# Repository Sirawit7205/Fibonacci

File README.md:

# Fibonacci
16-bit Fibonacci calculator with logic ICs

A circuit that calculates fibonacci up to 46,368 using only logic chips (except the display).

This project is mostly intended as a soldering practice because the PIC microcontroller featured on the board is fully capable of calculating fibonacci anyway without all the logic chips.

There are two versions of PCB, through-hole and SMD. Both versions use the same circuit and have the same physical size (4x6 inches: will fit most postcard frames).

The only difference is the PIC microcontroller used, both code also work the same way.

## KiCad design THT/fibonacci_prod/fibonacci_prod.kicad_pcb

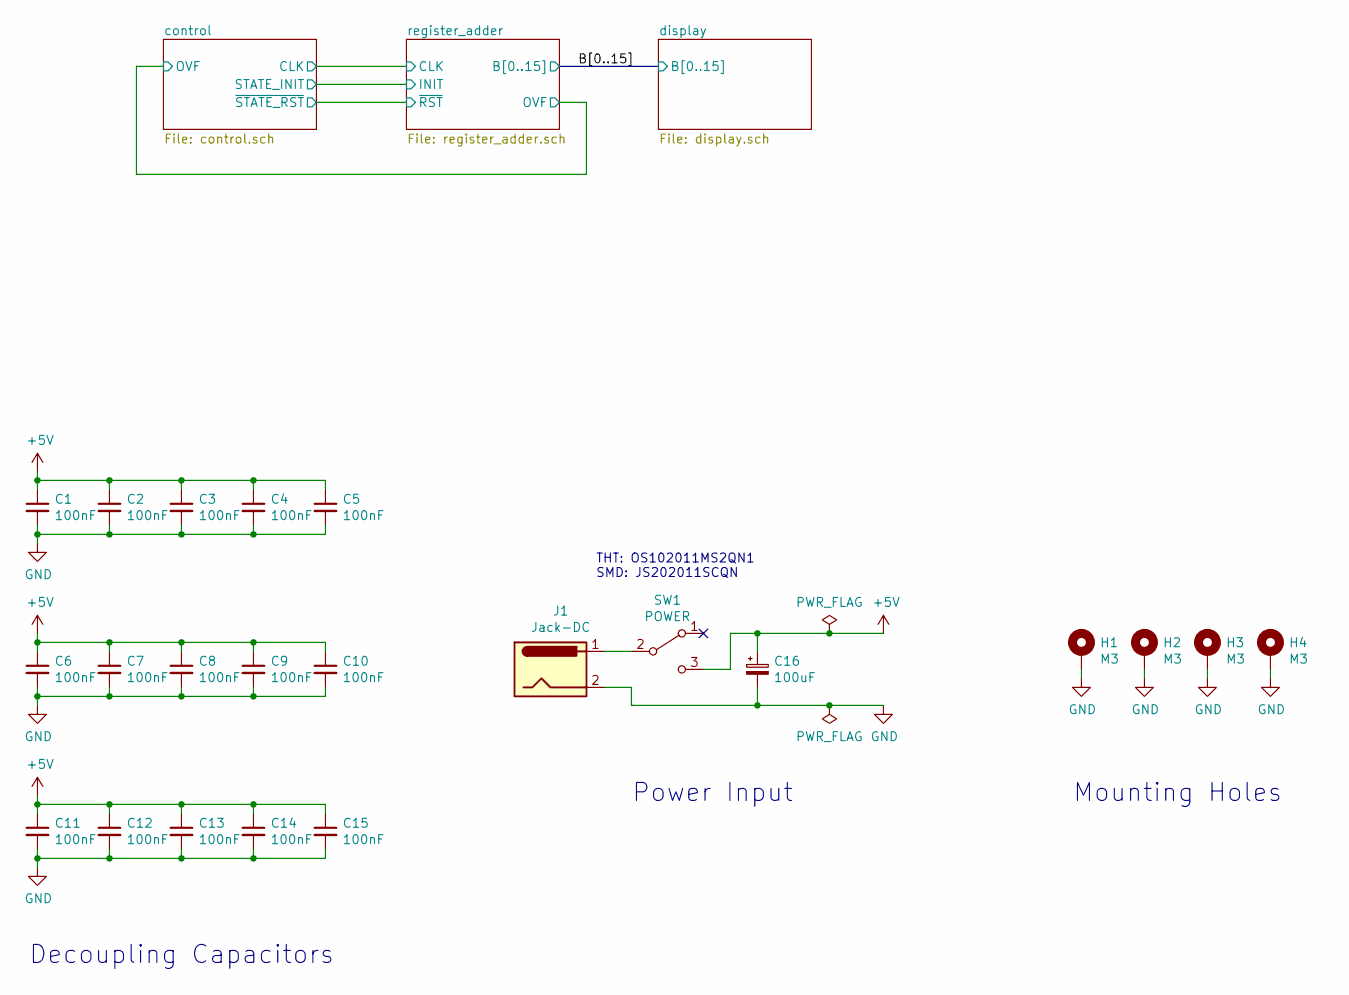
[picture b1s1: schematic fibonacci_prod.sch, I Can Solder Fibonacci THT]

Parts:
C1, C2, C3, C4, C5, C6, C7, C8, C9, C10, C11, C12, C13, C14, C15: 100nF; C_Disc_D5.1mm_W3.2mm_P5.00mm
C16: 100uF; CP_Radial_D6.3mm_P2.50mm
H1, H2, H3, H4: M3; MountingHole_3mm_Pad
J1: Jack-DC; BarrelJack_Horizontal
SW1: POWER; OS102011MS2QN1

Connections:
+5V: C1.1, C2.1, C3.1, C4.1, C5.1, C6.1, C7.1, C8.1, C9.1, C10.1, C11.1, C12.1, C13.1, C14.1, C15.1, C16.1, SW1.3 (C); also elsewhere on the board
GND: C1.2, C2.2, C3.2, C4.2, C5.2, C6.2, C7.2, C8.2, C9.2, C10.2, C11.2, C12.2, C13.2, C14.2, C15.2, C16.2, H1.1, H2.1, H3.1, H4.1, J1.2; also elsewhere on the board
unnamed: J1.1, SW1.2 (B)

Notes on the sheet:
Decoupling Capacitors
Power Input
THT: OS102011MS2QN1 SMD: JS202011SCQN
Mounting Holes

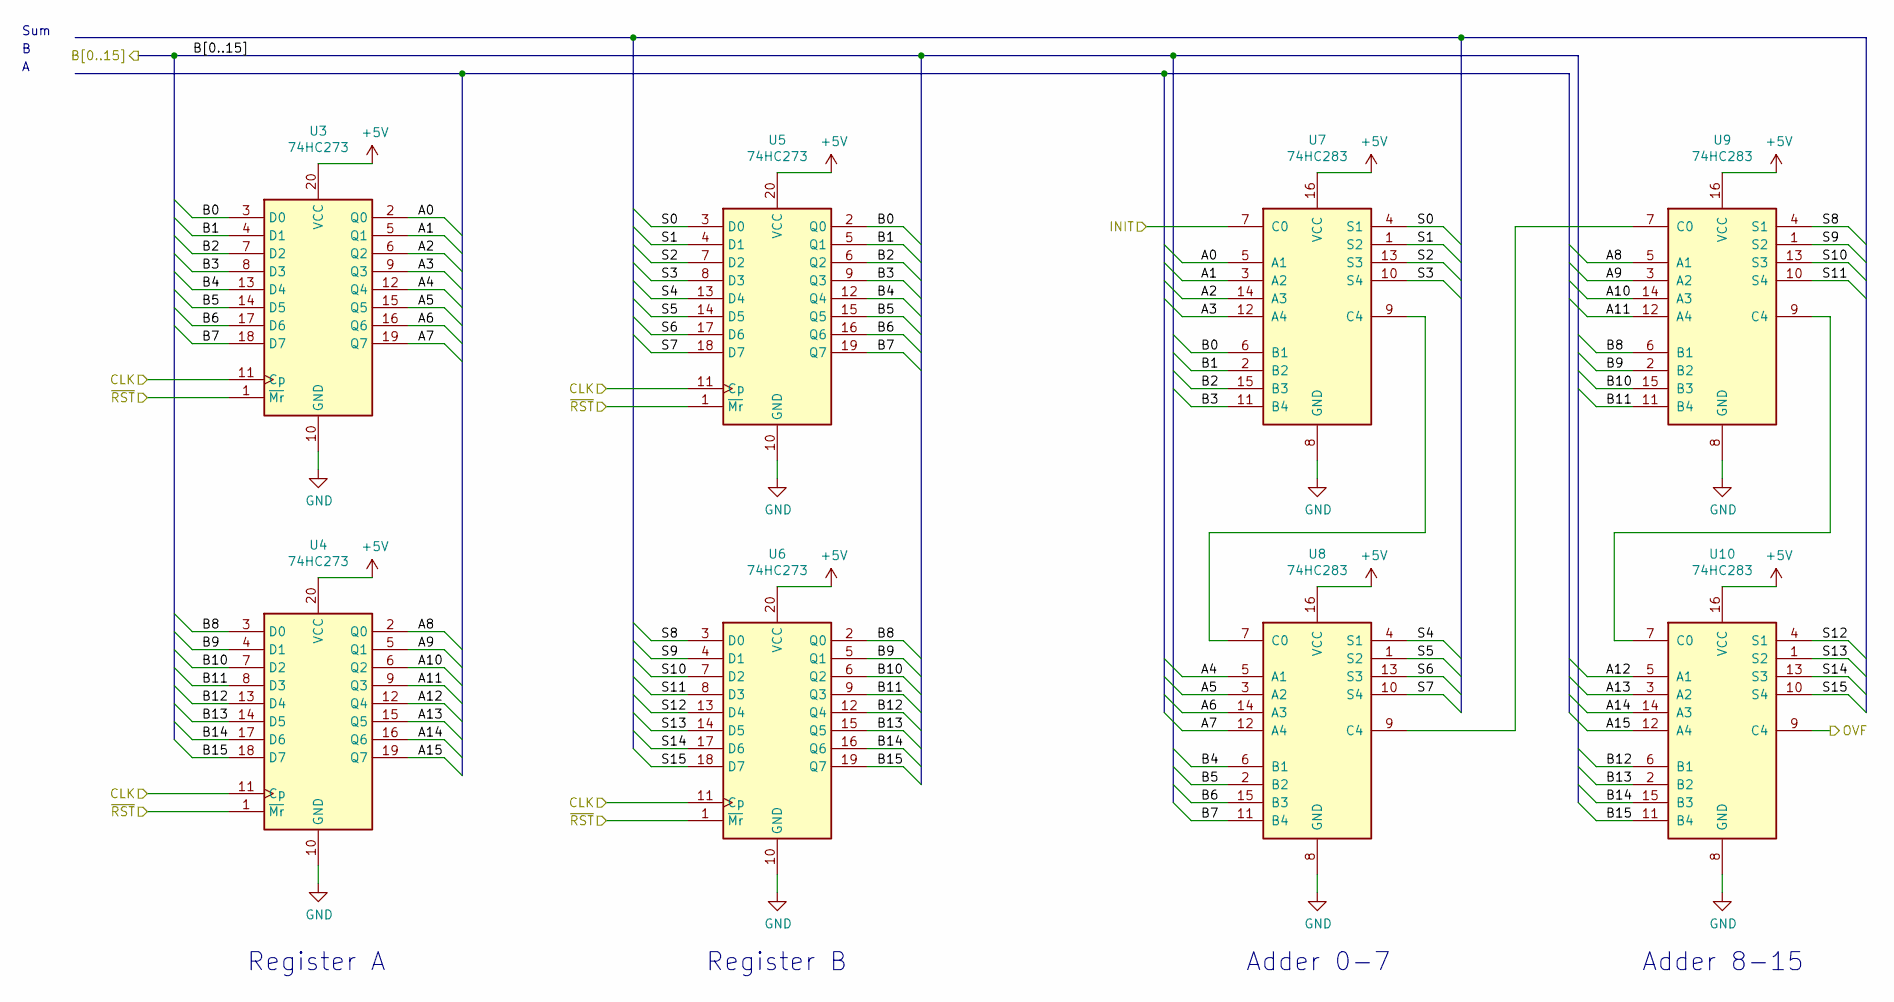
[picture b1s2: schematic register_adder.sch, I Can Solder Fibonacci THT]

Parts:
U3, U4, U5, U6: 74HC273; DIP-20_W7.62mm
U7, U8, U9, U10: 74HC283; DIP-16_W7.62mm

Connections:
+5V: U3.20 (VCC), U4.20 (VCC), U5.20 (VCC), U6.20 (VCC), U7.16 (VCC), U8.16 (VCC), U9.16 (VCC), U10.16 (VCC); also elsewhere on the board
/control/CLK: U3.11 (Cp), U4.11 (Cp), U5.11 (Cp), U6.11 (Cp); also elsewhere on the board
/control/OVF: U10.9 (C4); also elsewhere on the board
/display/B0: U3.3 (D0), U5.2 (Q0), U7.6 (B1); also elsewhere on the board
/display/B1: U3.4 (D1), U5.5 (Q1), U7.2 (B2); also elsewhere on the board
/display/B2: U3.7 (D2), U5.6 (Q2), U7.15 (B3); also elsewhere on the board
/display/B3: U3.8 (D3), U5.9 (Q3), U7.11 (B4); also elsewhere on the board
/display/B4: U3.13 (D4), U5.12 (Q4), U8.6 (B1); also elsewhere on the board
/display/B5: U3.14 (D5), U5.15 (Q5), U8.2 (B2); also elsewhere on the board
/display/B6: U3.17 (D6), U5.16 (Q6), U8.15 (B3); also elsewhere on the board
/display/B7: U3.18 (D7), U5.19 (Q7), U8.11 (B4); also elsewhere on the board
/display/B8: U4.3 (D0), U6.2 (Q0), U9.6 (B1); also elsewhere on the board
/display/B9: U4.4 (D1), U6.5 (Q1), U9.2 (B2); also elsewhere on the board
/display/B10: U4.7 (D2), U6.6 (Q2), U9.15 (B3); also elsewhere on the board
/display/B11: U4.8 (D3), U6.9 (Q3), U9.11 (B4); also elsewhere on the board
/display/B12: U4.13 (D4), U6.12 (Q4), U10.6 (B1); also elsewhere on the board
/display/B13: U4.14 (D5), U6.15 (Q5), U10.2 (B2); also elsewhere on the board
/display/B14: U4.17 (D6), U6.16 (Q6), U10.15 (B3); also elsewhere on the board
/display/B15: U4.18 (D7), U6.19 (Q7), U10.11 (B4); also elsewhere on the board
/register_adder/A0: U3.2 (Q0), U7.5 (A1)
/register_adder/A1: U3.5 (Q1), U7.3 (A2)
/register_adder/A2: U3.6 (Q2), U7.14 (A3)
/register_adder/A3: U3.9 (Q3), U7.12 (A4)
/register_adder/A4: U3.12 (Q4), U8.5 (A1)
/register_adder/A5: U3.15 (Q5), U8.3 (A2)
/register_adder/A6: U3.16 (Q6), U8.14 (A3)
/register_adder/A7: U3.19 (Q7), U8.12 (A4)
/register_adder/A8: U4.2 (Q0), U9.5 (A1)
/register_adder/A9: U4.5 (Q1), U9.3 (A2)
/register_adder/A10: U4.6 (Q2), U9.14 (A3)
/register_adder/A11: U4.9 (Q3), U9.12 (A4)
/register_adder/A12: U4.12 (Q4), U10.5 (A1)
/register_adder/A13: U4.15 (Q5), U10.3 (A2)
/register_adder/A14: U4.16 (Q6), U10.14 (A3)
/register_adder/A15: U4.19 (Q7), U10.12 (A4)
/register_adder/INIT: U7.7 (C0); also elsewhere on the board
/register_adder/S0: U5.3 (D0), U7.4 (S1)
/register_adder/S1: U5.4 (D1), U7.1 (S2)
/register_adder/S2: U5.7 (D2), U7.13 (S3)
/register_adder/S3: U5.8 (D3), U7.10 (S4)
/register_adder/S4: U5.13 (D4), U8.4 (S1)
/register_adder/S5: U5.14 (D5), U8.1 (S2)
/register_adder/S6: U5.17 (D6), U8.13 (S3)
/register_adder/S7: U5.18 (D7), U8.10 (S4)
/register_adder/S8: U6.3 (D0), U9.4 (S1)
/register_adder/S9: U6.4 (D1), U9.1 (S2)
/register_adder/S10: U6.7 (D2), U9.13 (S3)
/register_adder/S11: U6.8 (D3), U9.10 (S4)
/register_adder/S12: U6.13 (D4), U10.4 (S1)
/register_adder/S13: U6.14 (D5), U10.1 (S2)
/register_adder/S14: U6.17 (D6), U10.13 (S3)
/register_adder/S15: U6.18 (D7), U10.10 (S4)
/register_adder/~RST: U3.1 (~Mr), U4.1 (~Mr), U5.1 (~Mr), U6.1 (~Mr); also elsewhere on the board
GND: U3.10 (GND), U4.10 (GND), U5.10 (GND), U6.10 (GND), U7.8 (GND), U8.8 (GND), U9.8 (GND), U10.8 (GND); also elsewhere on the board
unnamed: U7.9 (C4), U8.7 (C0)
unnamed: U8.9 (C4), U9.7 (C0)
unnamed: U9.9 (C4), U10.7 (C0)

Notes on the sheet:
Adder 0-7
Adder 8-15
Register B
Register A
Sum

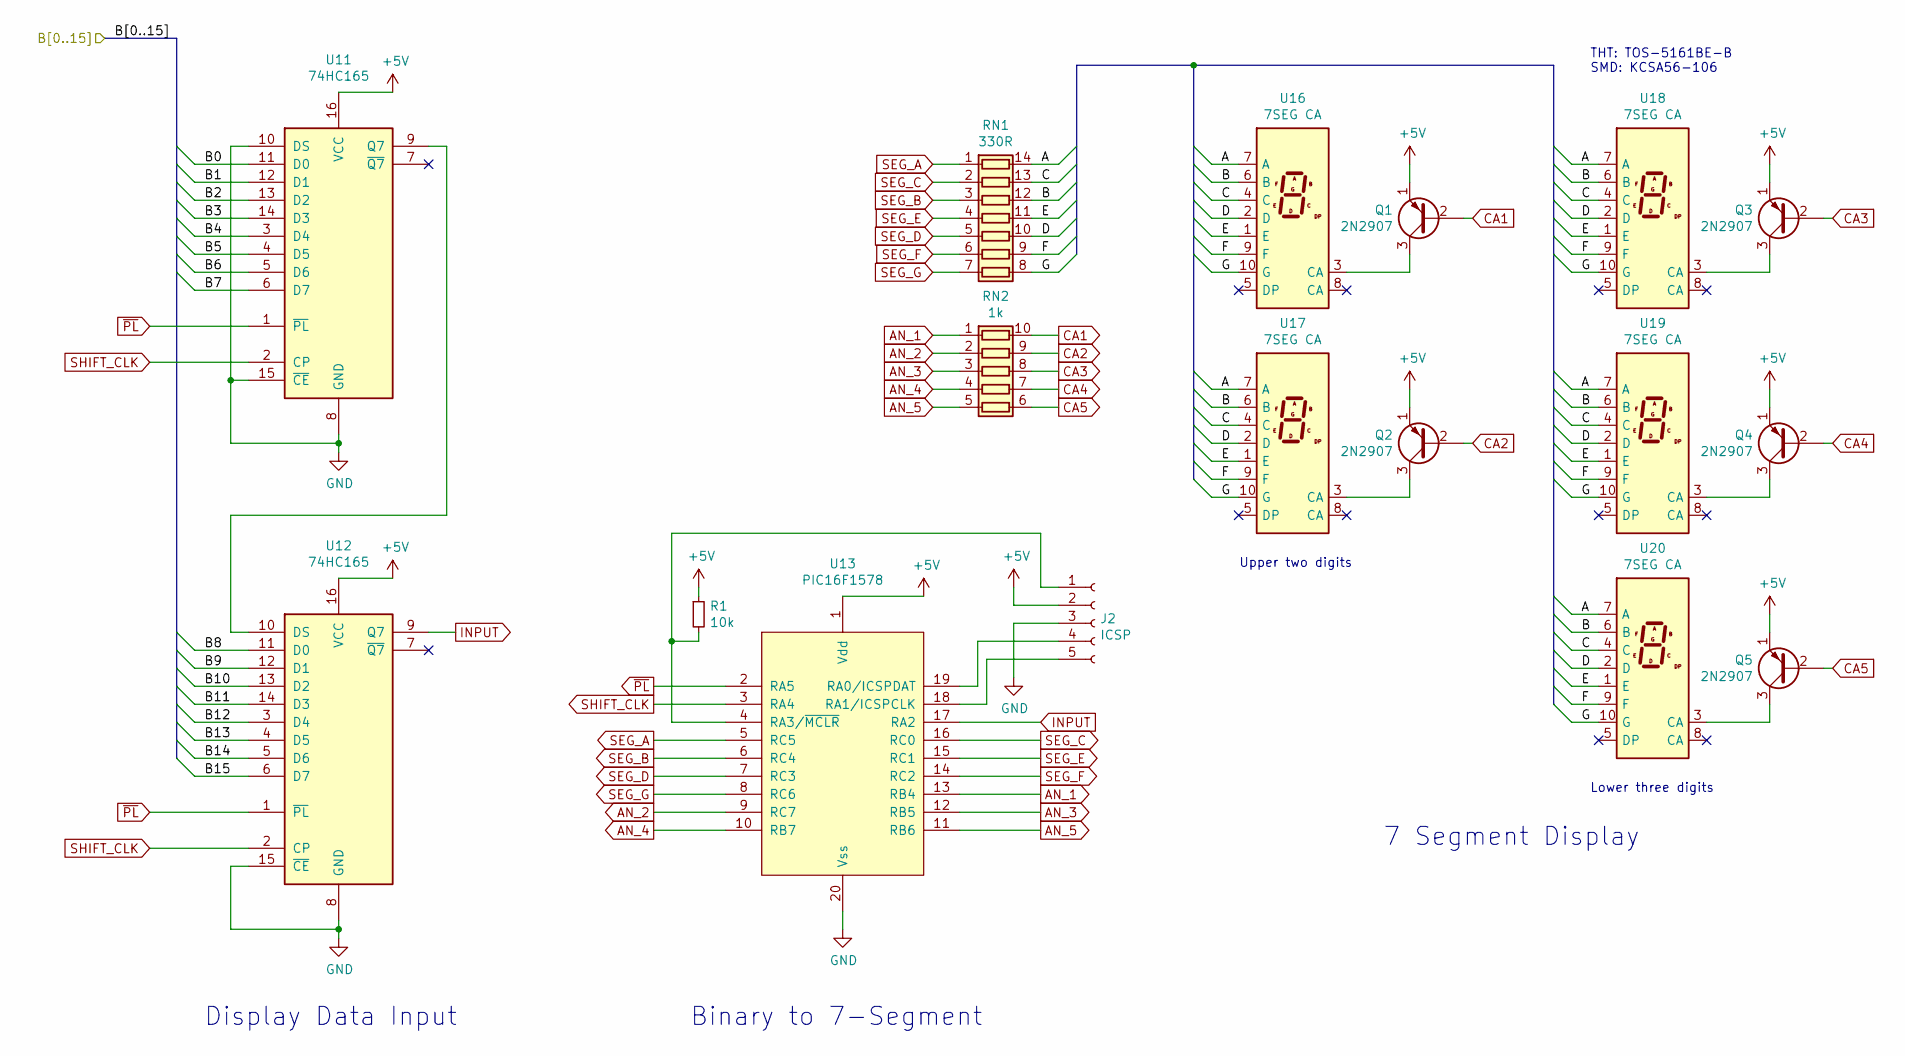
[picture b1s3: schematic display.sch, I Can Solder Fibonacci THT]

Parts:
J2: ICSP; PinHeader_1x05_P2.54mm_Vertical
Q1, Q2, Q3, Q4, Q5: 2N2907; TO-92
R1: 10k; R_Axial_DIN0207_L6.3mm_D2.5mm_P7.62mm_Horizontal
RN1: 330R; DIP-14_W7.62mm_Socket
RN2: 1k; DIP-10_W7.62mm_Socket
U11, U12: 74HC165; DIP-16_W7.62mm
U13: PIC16F1578; DIP-20_W7.62mm
U16, U17, U18, U19, U20: 7SEG CA; 7SegmentLED_LTS6760_LTS6780

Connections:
+5V: J2.2, Q1.1 (E), Q2.1 (E), Q3.1 (E), Q4.1 (E), Q5.1 (E), R1.1, U11.16 (VCC), U12.16 (VCC), U13.1 (Vdd); also elsewhere on the board
/display/A: RN1.14 (R1.2), U16.7 (A), U17.7 (A), U18.7 (A), U19.7 (A), U20.7 (A)
/display/B: RN1.12 (R3.2), U16.6 (B), U17.6 (B), U18.6 (B), U19.6 (B), U20.6 (B)
/display/B0: U11.11 (D0); also elsewhere on the board
/display/B1: U11.12 (D1); also elsewhere on the board
/display/B2: U11.13 (D2); also elsewhere on the board
/display/B3: U11.14 (D3); also elsewhere on the board
/display/B4: U11.3 (D4); also elsewhere on the board
/display/B5: U11.4 (D5); also elsewhere on the board
/display/B6: U11.5 (D6); also elsewhere on the board
/display/B7: U11.6 (D7); also elsewhere on the board
/display/B8: U12.11 (D0); also elsewhere on the board
/display/B9: U12.12 (D1); also elsewhere on the board
/display/B10: U12.13 (D2); also elsewhere on the board
/display/B11: U12.14 (D3); also elsewhere on the board
/display/B12: U12.3 (D4); also elsewhere on the board
/display/B13: U12.4 (D5); also elsewhere on the board
/display/B14: U12.5 (D6); also elsewhere on the board
/display/B15: U12.6 (D7); also elsewhere on the board
/display/C: RN1.13 (R2.2), U16.4 (C), U17.4 (C), U18.4 (C), U19.4 (C), U20.4 (C)
/display/D: RN1.10 (R5.2), U16.2 (D), U17.2 (D), U18.2 (D), U19.2 (D), U20.2 (D)
/display/E: RN1.11 (R4.2), U16.1 (E), U17.1 (E), U18.1 (E), U19.1 (E), U20.1 (E)
/display/F: RN1.9 (R6.2), U16.9 (F), U17.9 (F), U18.9 (F), U19.9 (F), U20.9 (F)
/display/G: RN1.8 (R7.2), U16.10 (G), U17.10 (G), U18.10 (G), U19.10 (G), U20.10 (G)
AN_1: RN2.1 (R1.1), U13.13 (RB4)
AN_2: RN2.2 (R2.1), U13.9 (RC7)
AN_3: RN2.3 (R3.1), U13.12 (RB5)
AN_4: RN2.4 (R4.1), U13.10 (RB7)
AN_5: RN2.5 (R5.1), U13.11 (RB6)
CA1: Q1.2 (B), RN2.10 (R1.2)
CA2: Q2.2 (B), RN2.9 (R2.2)
CA3: Q3.2 (B), RN2.8 (R3.2)
CA4: Q4.2 (B), RN2.7 (R4.2)
CA5: Q5.2 (B), RN2.6 (R5.2)
GND: J2.3, U11.8 (GND), U11.10 (DS), U11.15 (~CE), U12.8 (GND), U12.15 (~CE), U13.20 (Vss); also elsewhere on the board
INPUT: U12.9 (Q7), U13.17 (RA2)
unnamed: J2.1, R1.2, U13.4 (RA3/~MCLR)
unnamed: J2.4, U13.19 (RA0/ICSPDAT)
unnamed: J2.5, U13.18 (RA1/ICSPCLK)
unnamed: Q1.3 (C), U16.3 (CA)
unnamed: Q2.3 (C), U17.3 (CA)
unnamed: Q3.3 (C), U18.3 (CA)
unnamed: Q4.3 (C), U19.3 (CA)
unnamed: Q5.3 (C), U20.3 (CA)
unnamed: U11.9 (Q7), U12.10 (DS)
SEG_A: RN1.1 (R1.1), U13.5 (RC5)
SEG_B: RN1.3 (R3.1), U13.6 (RC4)
SEG_C: RN1.2 (R2.1), U13.16 (RC0)
SEG_D: RN1.5 (R5.1), U13.7 (RC3)
SEG_E: RN1.4 (R4.1), U13.15 (RC1)
SEG_F: RN1.6 (R6.1), U13.14 (RC2)
SEG_G: RN1.7 (R7.1), U13.8 (RC6)
SHIFT_CLK: U11.2 (CP), U12.2 (CP), U13.3 (RA4)
~PL: U11.1 (~PL), U12.1 (~PL), U13.2 (RA5)

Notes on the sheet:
THT: TOS-5161BE-B SMD: KCSA56-106
Upper two digits
Lower three digits
7 Segment Display
Display Data Input
Binary to 7-Segment

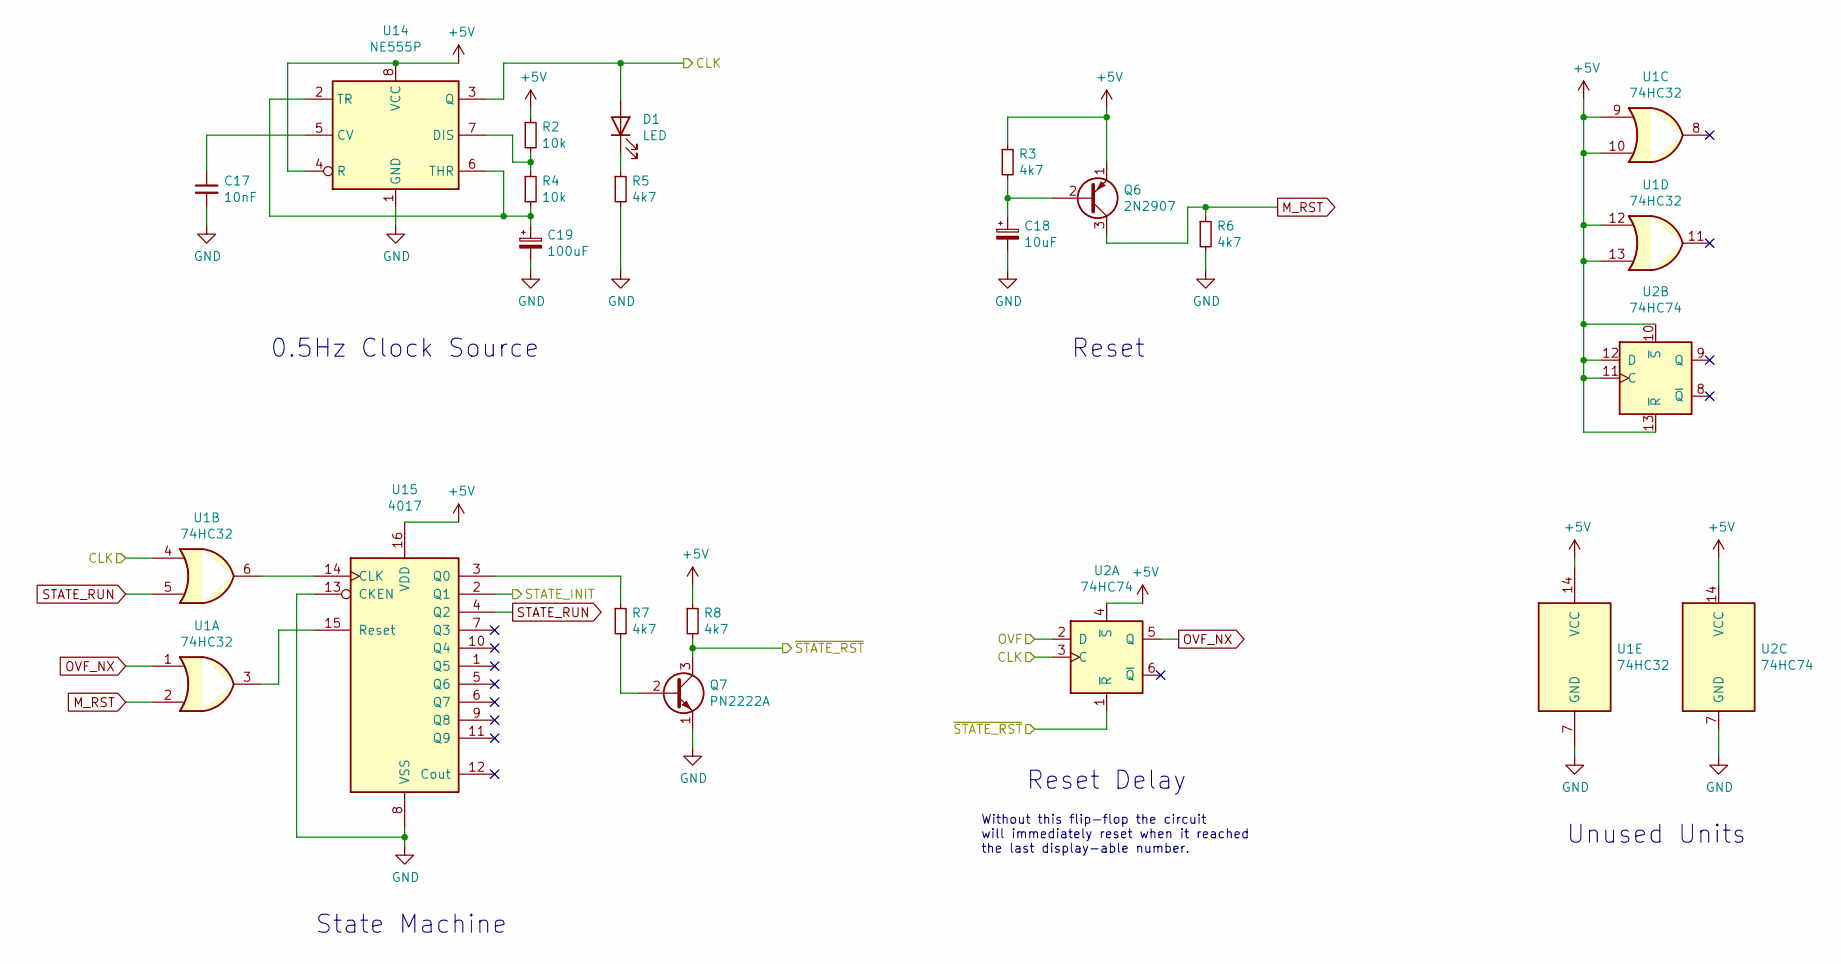
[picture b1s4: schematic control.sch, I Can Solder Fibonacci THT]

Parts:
C17: 10nF; C_Disc_D5.1mm_W3.2mm_P5.00mm
C18: 10uF; CP_Radial_D5.0mm_P2.00mm
C19: 100uF; CP_Radial_D6.3mm_P2.50mm
D1: LED; LED_D3.0mm
Q6: 2N2907; TO-92
Q7: PN2222A; TO-92
R2, R4: 10k; R_Axial_DIN0207_L6.3mm_D2.5mm_P2.54mm_Vertical
R3, R6: 4k7; R_Axial_DIN0207_L6.3mm_D2.5mm_P2.54mm_Vertical
R5, R7, R8: 4k7; R_Axial_DIN0207_L6.3mm_D2.5mm_P7.62mm_Horizontal
U1: 74HC32; DIP-14_W7.62mm
U2: 74HC74; DIP-14_W7.62mm
U14: NE555P; DIP-8_W7.62mm
U15: 4017; DIP-16_W7.62mm

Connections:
+5V: Q6.1 (E), R2.1, R3.1, R8.1, U1.9, U1.10, U1.12, U1.13, U1.14 (VCC), U2.4 (~S), U2.10 (~S), U2.11 (C), U2.12 (D), U2.13 (~R), U2.14 (VCC), U14.4 (R), U14.8 (VCC), U15.16 (VDD); also elsewhere on the board
/control/CLK: D1.2 (A), U1.4, U2.3 (C), U14.3 (Q); also elsewhere on the board
/control/OVF: U2.2 (D); also elsewhere on the board
/register_adder/INIT: U15.2 (Q1); also elsewhere on the board
/register_adder/~RST: Q7.3 (C), R8.2, U2.1 (~R); also elsewhere on the board
GND: C17.2, C18.2, C19.2, Q7.1 (E), R5.2, R6.2, U1.7 (GND), U2.7 (GND), U14.1 (GND), U15.8 (VSS), U15.13 (CKEN); also elsewhere on the board
M_RST: Q6.3 (C), R6.1, U1.2
unnamed: C17.1, U14.5 (CV)
unnamed: C18.1, Q6.2 (B), R3.2
unnamed: C19.1, R4.2, U14.2 (TR), U14.6 (THR)
unnamed: D1.1 (K), R5.1
unnamed: Q7.2 (B), R7.2
unnamed: R2.2, R4.1, U14.7 (DIS)
unnamed: R7.1, U15.3 (Q0)
unnamed: U1.3, U15.15 (Reset)
unnamed: U1.6, U15.14 (CLK)
OVF_NX: U1.1, U2.5 (Q)
STATE_RUN: U1.5, U15.4 (Q2)

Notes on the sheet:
0.5Hz Clock Source
Reset
State Machine
Reset Delay
Without this flip-flop the circuit will immediately reset when it reached the last display-able number.
Unused Units

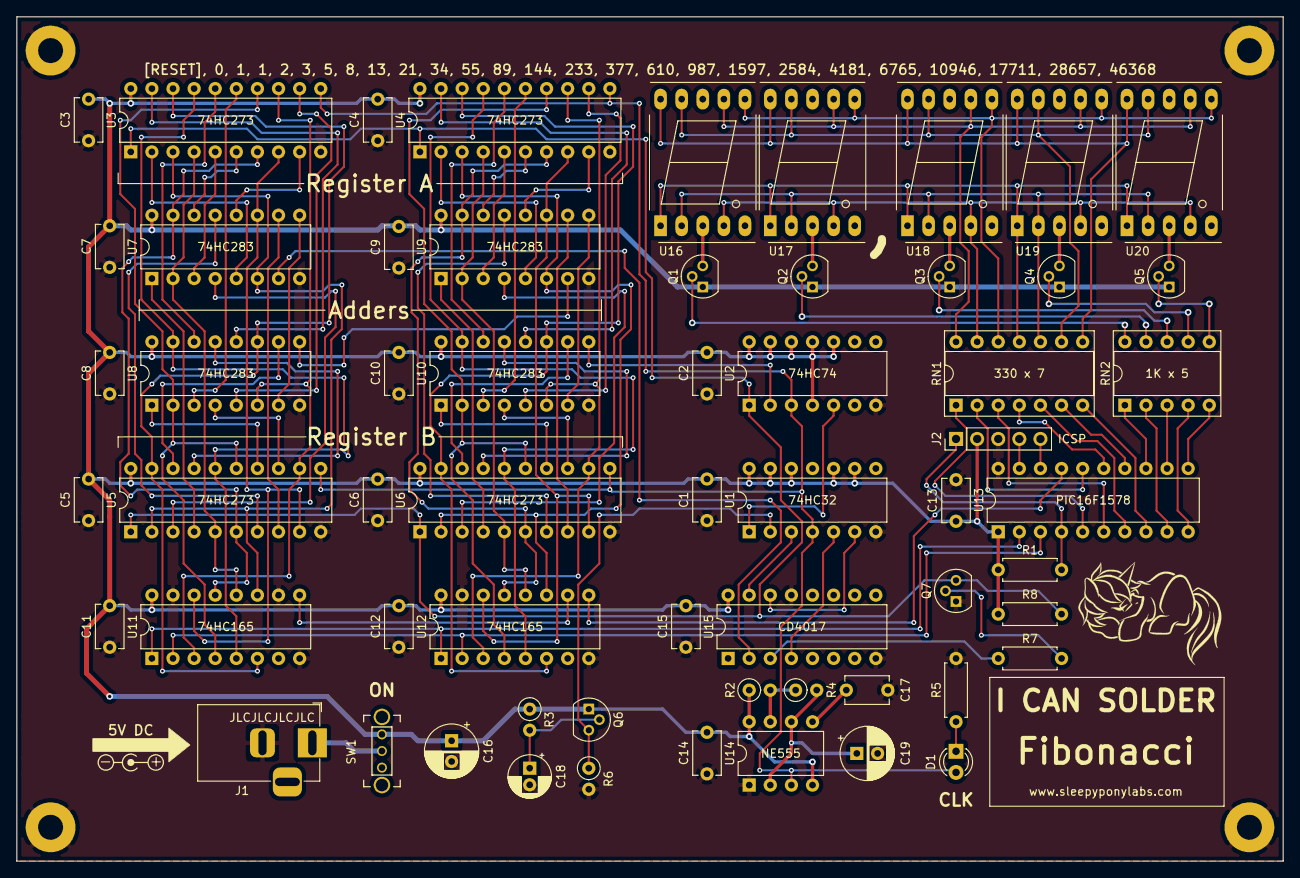
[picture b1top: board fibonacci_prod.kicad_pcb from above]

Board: 2 copper layers, 152.4 x 101.6 mm, 64 parts (0 on the bottom side), 106 nets.

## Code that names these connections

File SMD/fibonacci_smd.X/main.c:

/*
 *  7-segment multiplexing
 * 
 *  RA0 = ICSPDAT
 *  RA1 = ICSPCLK
 *  RA2 = Serial input
 *  RA3 = MCLR
 *  RA4 = Shift clock
 *  RA5 = Parallel load
 *  RB4 = Anode 1
 *  RB5 = Anode 3
 *  RB6 = Anode 5
 *  RB7 = Anode 4
 *  RC7 = Anode 2
 *  
 *  PORTC = Cathode (-,G,A,B,D,F,E,C)
 */

// PIC16F721 Configuration Bit Settings

// 'C' source line config statements

// CONFIG1
#pragma config FOSC = INTOSCIO  // Oscillator Selection bits (INTOSCIO oscillator: I/O function on RA4/CLKO pin, I/O function on RA5/CLKI)
#pragma config WDTE = ON        // Watchdog Timer Enable bit (WDT enabled)
#pragma config PWRTE = OFF      // Power-up Timer Enable bit (PWRT disabled)
#pragma config MCLRE = ON       // RA3/MCLR/VPP Pin Function Select bit (RA3/MCLR/VPP pin function is MCLR; Weak pull-up enabled.)
#pragma config CP = OFF         // Flash Program Memory Code Protection bit (Code protection off)
#pragma config BOREN = ON       // Brown-out Reset Enable bits (Brown-out Reset enabled)
#pragma config PLLEN = ON       // INTOSC PLLEN Enable Bit (INTOSC Frequency is 16 MHz (32x))

// CONFIG2
#pragma config WRTEN = OFF      // Flash memory self-write protection bits (Write protection off)

// #pragma config statements should precede project file includes.
// Use project enums instead of #define for ON and OFF.

#define _XTAL_FREQ 4000000

#include <xc.h>
#include <stdint.h>

unsigned char digits[10] = {0xC0, 0xEE, 0x85, 0x86, 0xAA, 0x92, 0x90, 0xCA, 0x80, 0x82};

#define PL RA5
#define SCLK RA4
#define SDAT RA2
#define AN1 RB4
#define AN2 RC7
#define AN3 RB5
#define AN4 RB7
#define AN5 RB6

uint16_t getNumber() {
    uint16_t output = 0;
    
    //parallel load
    PL = 0;
    __delay_us(1);
    PL = 1;
    __delay_us(1);
    
    for(int i = 0; i < 16; i++) {
        //shift current bit in
        output = (output << 1) | SDAT;
        
        //shift next bit out
        SCLK = 1;
        __delay_us(1);
        SCLK = 0;
        __delay_us(1);
    }
    
    return output;
}

void main(void) {
    //chip setup
    OSCCON |= _OSCCON_IRCF0_MASK;               //set INTOSC speed to 4 MHz
    OSCCON &= ~_OSCCON_IRCF1_MASK;
    OPTION_REG &= ~_OPTION_REG_nRABPU_MASK;     //global enable port pull-ups
    WPUA |= _WPUA_WPUA2_MASK;                   //enable pull-up on RA2
    ANSELA &= 0x00;                             //disable analog input on all ports
    ANSELB &= 0x00;
    ANSELC &= 0x00;
    TRISA &= 0x04;                              //port A as output except RA2
    TRISB &= 0x00;                              //port B as output
    TRISC &= 0x00;                              //port C as output
    PORTA |= 0xEB;                              //port A all high except RA2, RA4 (shift clock low, parallel load high)
    PORTB |= 0xFF;                              //port B all high (disable anodes)
    PORTC |= 0xFF;                              //port C all high (disable cathodes and anode 2)

    while(1)
    {
        asm("CLRWDT");  //clear WDT
        
        uint16_t num = getNumber();
        
        //digit 1
        PORTC = digits[num / 10000];
        num = num % 10000;
        AN1 = 0;
        __delay_ms(2);
        AN1 = 1;

        //digit 2
        PORTC = digits[num / 1000];
        num = num % 1000;
        AN2 = 0;
        __delay_ms(2);
        AN2 = 1;
        
        //digit 3
        PORTC = digits[num / 100];
        num = num % 100;
        AN3 = 0;
        __delay_ms(2);
        AN3 = 1;

        //digit 4
        PORTC = digits[num / 10];
        num = num % 10;
        AN4 = 0;
        __delay_ms(2);
        AN4 = 1;

        //digit 5
        PORTC = digits[num];
        AN5 = 0;
        __delay_ms(2);
        AN5 = 1;
    }
    
    return;
}

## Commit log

2022-05-16 fixed incorrect project names
2022-05-16 add firmware
